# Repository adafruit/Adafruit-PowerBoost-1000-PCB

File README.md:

## Adafruit PowerBoost 1000 Basic PCB
<a href="http://www.adafruit.com/products/2030"><br/>
Click here to purchase one from the Adafruit shop</a>

PowerBoost is the perfect power supply for your power-hungry portable project! This little DC/DC boost converter module can run from 1.8V batteries or higher, and convert that voltage to 5.2V DC for running your 5V projects. With a beefy 4A DC/DC converter, it can give you 1A+ from as low as 2V. 

Like our popular 5V 1A USB wall adapter, we tweaked the output to be 5.2V instead of a straight-up 5.0V so that there's a little bit of 'headroom' long cables, high draw, the addition of a diode on the output if you wish, etc. The 5.2V is safe for all 5V-powered electronics like Arduino, Raspberry Pi, or BeagleBone while preventing icky brown-outs during high current draw because of USB cable resistance.

The PowerBoost 1000 has at the heart a TPS61030 boost converter from TI. This boost converter chip has some really nice extras such as low battery detection, 4A internal switch, synchronous conversion, excellent efficiency, and 700KHz high-frequency operation. Check out these specs!

PCB files for Adafruit PowerBoost 1000 Basic (no charger)
- https://www.adafruit.com/products/2030

### License

Adafruit invests time and resources providing this open source design, please support Adafruit and open-source hardware by purchasing products from [Adafruit](https://www.adafruit.com)!

All text above must be included in any redistribution

Designed by Limor Fried/Ladyada for Adafruit Industries.
Creative Commons Attribution/Share-Alike, all text above must be included in any redistribution. 
See license.txt for additional information.

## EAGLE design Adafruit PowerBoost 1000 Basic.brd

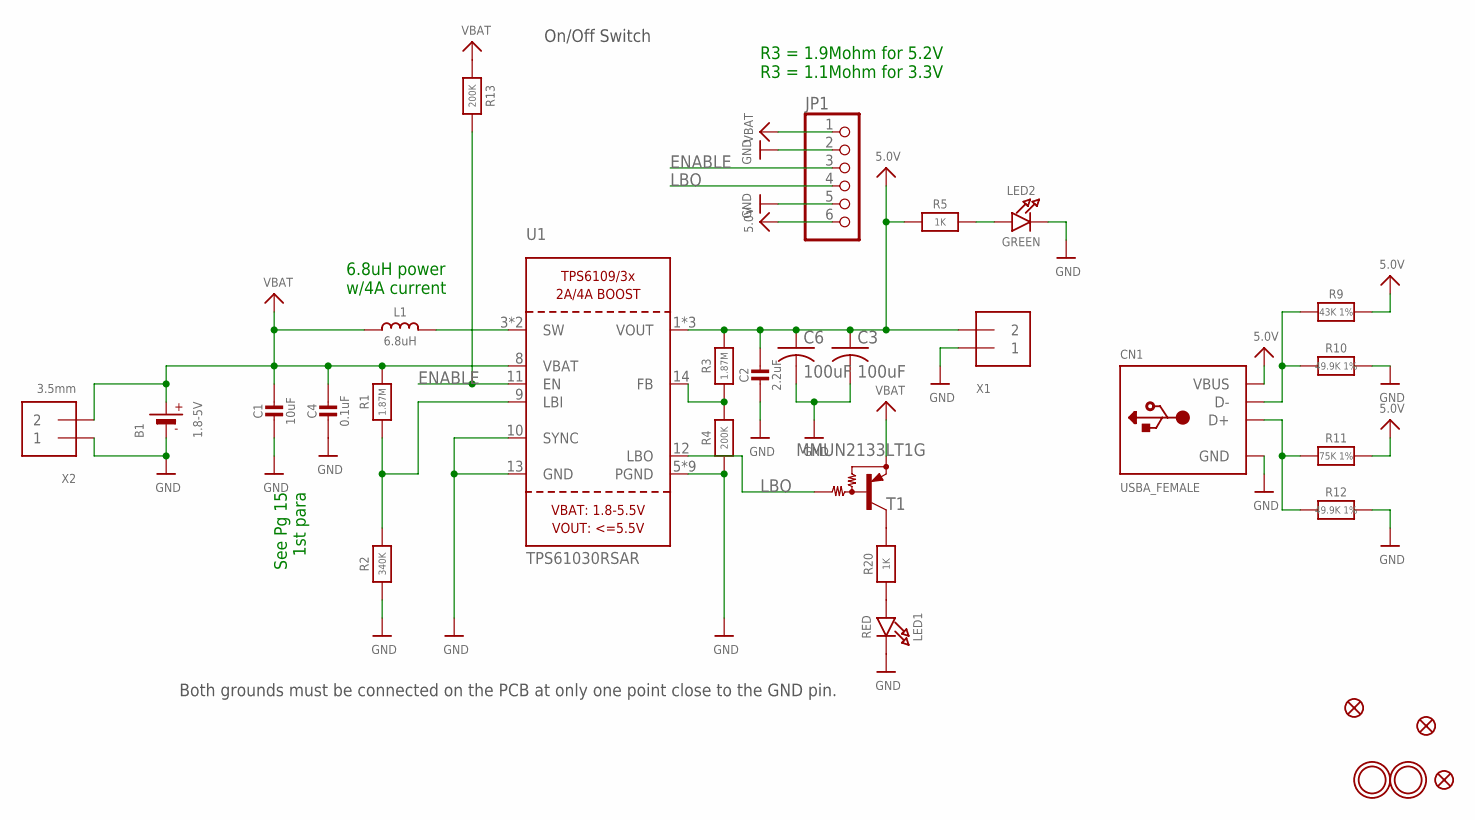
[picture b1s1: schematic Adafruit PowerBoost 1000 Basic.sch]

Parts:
B1: 1.8-5V; JSTPH2
C1: 10uF; 0805-NO
C2: 2.2uF; 0805-NO
C3, C6: 100uF; C1210
C4: 0.1uF; 0805-NO
CN1: USBA_FEMALE; USB_HOST-PTH
FID1, FID2, FID3: FIDUCIAL""; FIDUCIAL_1MM
JP1: PINHD-1X6CB; 1X06-CLEANBIG
L1: 6.8uH; INDUCTOR_8X8MM
LED1: RED; CHIPLED_0805_NOOUTLINE
LED2: GREEN; CHIPLED_0805_NOOUTLINE
R1, R3: 1.87M; _0805MP
R2: 340K; _0805MP
R4, R13: 200K; 0805-NO
R5, R20: 1K; 0805-NO
R9: 43K 1%; 0805-NO
R10, R12: 49.9K 1%; 0805-NO
R11: 75K 1%; 0805-NO
T1: MMUN2133LT1G; SC59-BEC
U1: TPS61030RSAR; PVQFN-16
U$10, U$11: MOUNTINGHOLE2.5; MOUNTINGHOLE_2.5_PLATED
X1: TERMBLOCK_1X2; TERMBLOCK_1X2-3.5MM
X2: 3.5mm; TERMBLOCK_1X2-3.5MM

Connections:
5.0V: C2.1, C3.1, C6.1, CN1.VBUS, JP1.6, R3.2, R5.1, R9.2, R11.2, U1.1 (VOUT), U1.15 (VOUT), U1.16 (VOUT), X1.2
D+: CN1.D+, R11.1, R12.1
D-: CN1.D-, R9.1, R10.1
ENABLE: JP1.3, R13.2, U1.11 (EN)
GND: B1.1 (-), C1.2, C2.2, C3.2, C4.2, C6.2, CN1.GND, JP1.2, JP1.5, LED1.C, LED2.C, R2.1, R4.1, R10.2, R12.2, U1.5 (PGND), U1.6 (PGND), U1.7 (PGND), U1.10 (SYNC), U1.13 (GND), U1.P$18 (PGND), U1.P$19 (PGND), U1.P$20 (PGND), U1.P$21 (PGND), U1.P$22 (PGND), U1.THERMAL (PGND), X1.1, X2.1
LBO: JP1.4, T1.B, U1.12 (LBO)
unnamed: L1.P$2 (2), U1.3 (SW), U1.4 (SW)
unnamed: LED1.A, R20.1
unnamed: R1.1, R2.2, U1.9 (LBI)
unnamed: LED2.A, R5.2
unnamed: R3.1, R4.2, U1.14 (FB)
unnamed: R20.2, T1.C
VBAT: B1.2 (+), C1.1, C4.1, JP1.1, L1.P$1 (1), R1.2, R13.1, T1.E, U1.8 (VBAT), X2.2

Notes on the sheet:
Both grounds must be connected on the PCB at only one point close to the GND pin.
On/Off Switch
See Pg 15 1st para
6.8uH power w/4A current
R3 = 1.9Mohm for 5.2V R3 = 1.1Mohm for 3.3V

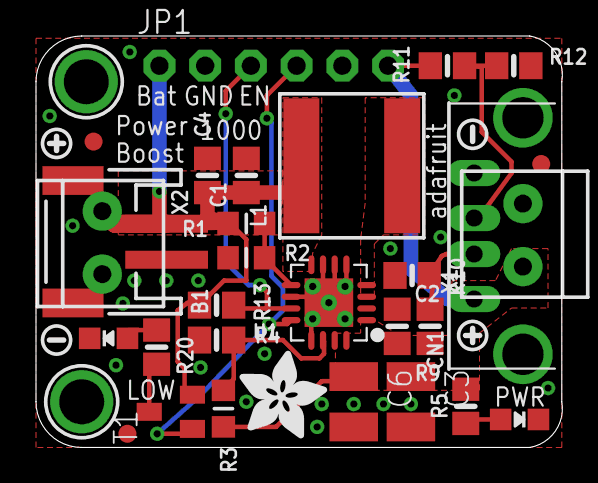
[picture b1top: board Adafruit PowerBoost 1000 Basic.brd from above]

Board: 2 copper layers, 29.2 x 22.9 mm, 37 parts (1 on the bottom side), 13 nets.

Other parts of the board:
U$12, U$26: SYMBOL_MINUS
U$13, U$25: SYMBOL_PLUS
U$28, U$33: ADAFRUIT_5MM

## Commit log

2016-01-25 init

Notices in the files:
parts and their libraries:
microbuilder: This work is placed in the public domain, and may be freely used for commercial and non-commercial work with the following conditions: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
